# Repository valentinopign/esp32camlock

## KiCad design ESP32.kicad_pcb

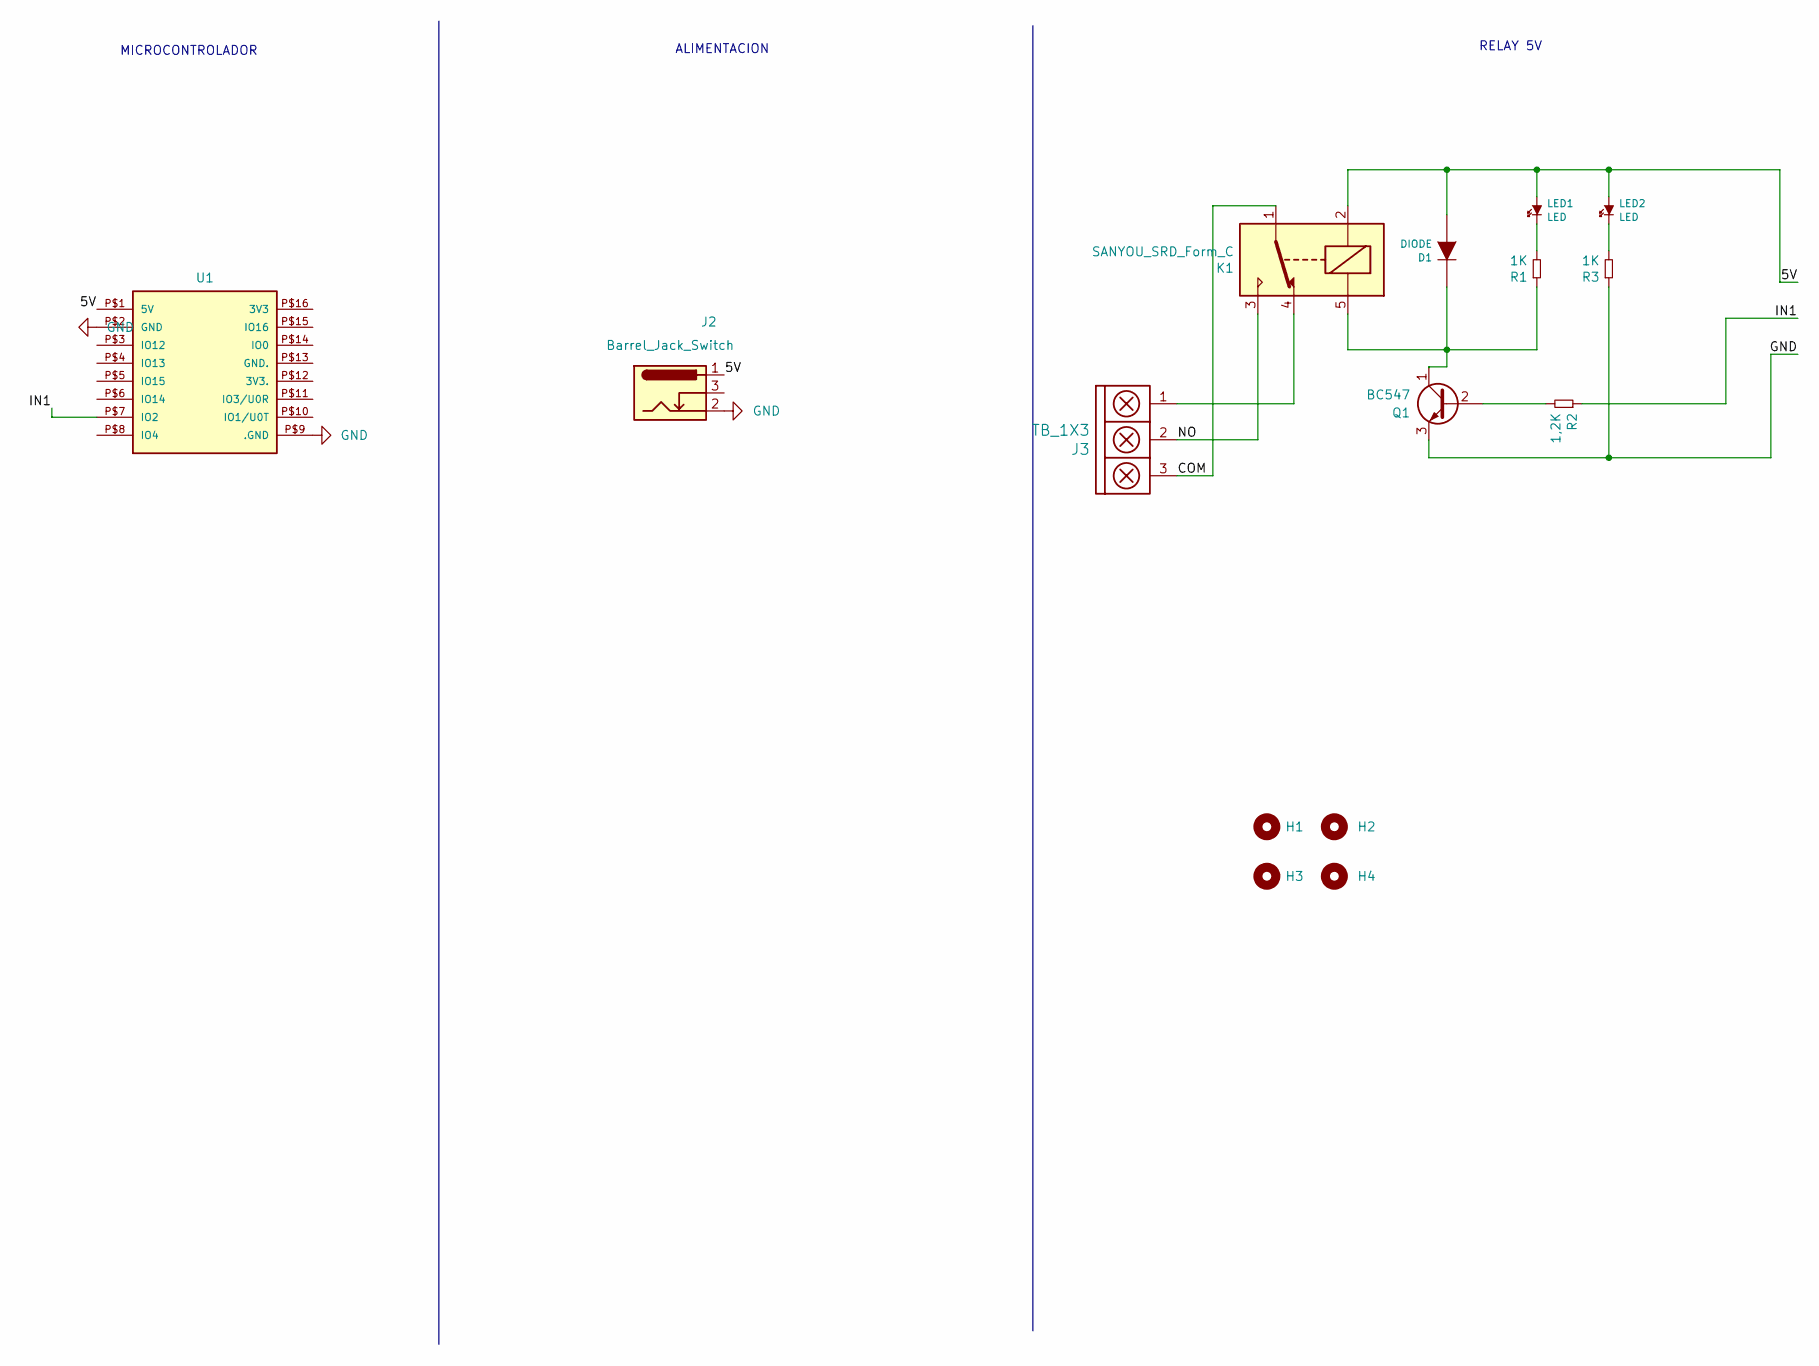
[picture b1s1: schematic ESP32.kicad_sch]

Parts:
D1: DIODE; DO-41
H1, H2, H3, H4: Mounting_Hole; hole_2mm
J2: Barrel_Jack_Switch; BarrelJack_Horizontal
J3: TB_1X3; BORNERA3
K1: SANYOU_SRD_Form_C; Relay_C
LED1, LED2: LED; led_3mm_red
Q1: BC547; TO-92
R1, R3: 1K; RES0.2
R2: 1,2K; RES0.2
U1: ESP32-CAM

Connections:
/5V: D1.1 (A), J2.1, K1.2, LED1.1 (A), LED2.1 (A), U1.P$1 (5V)
/COM: J3.3, K1.1
/IN1: R2.1, U1.P$7 (IO2)
/NO: J3.2, K1.3
GND: J2.2, Q1.3 (E), R3.1, U1.P$2 (GND), U1.P$9 (.GND)
unnamed: D1.2 (K), K1.5, Q1.1 (C), R1.1
unnamed: J3.1, K1.4
unnamed: LED1.2 (K), R1.2
unnamed: LED2.2 (K), R3.2
unnamed: Q1.2 (B), R2.2

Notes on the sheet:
MICROCONTROLADOR
RELAY 5V
ALIMENTACION

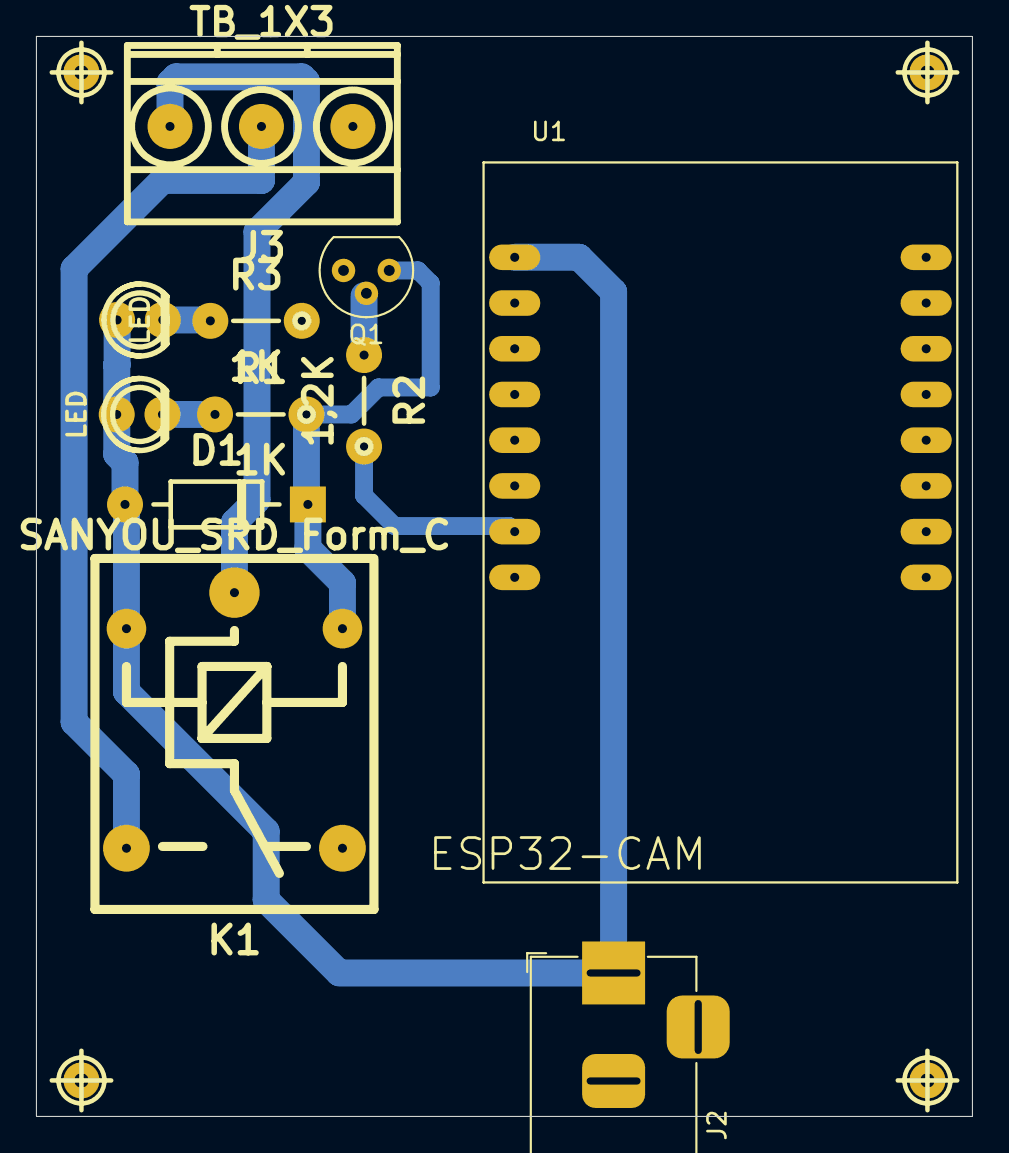
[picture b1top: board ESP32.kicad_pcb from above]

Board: 2 copper layers, 52.0 x 60.0 mm, 15 parts (0 on the bottom side), 10 nets.

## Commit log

2022-07-14 Activacion RELAY,WEB
    1/4
2022-07-14 Codigo APP
    2/4
2022-07-14 Codigo Index para la camara
    3/4
2022-07-14 Codigo PINSesp
    4/4
2022-07-14 Codigo esp32camlock
    Codigo completo para la activacion de la web y el relay
2022-07-14 Schematic y PCB del proyecto
